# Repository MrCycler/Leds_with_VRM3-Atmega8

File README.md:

# Leds_with_VRM3
Proyecto de manejo de leds con Voice recogniction module V.3 usando un ATMEGA8.

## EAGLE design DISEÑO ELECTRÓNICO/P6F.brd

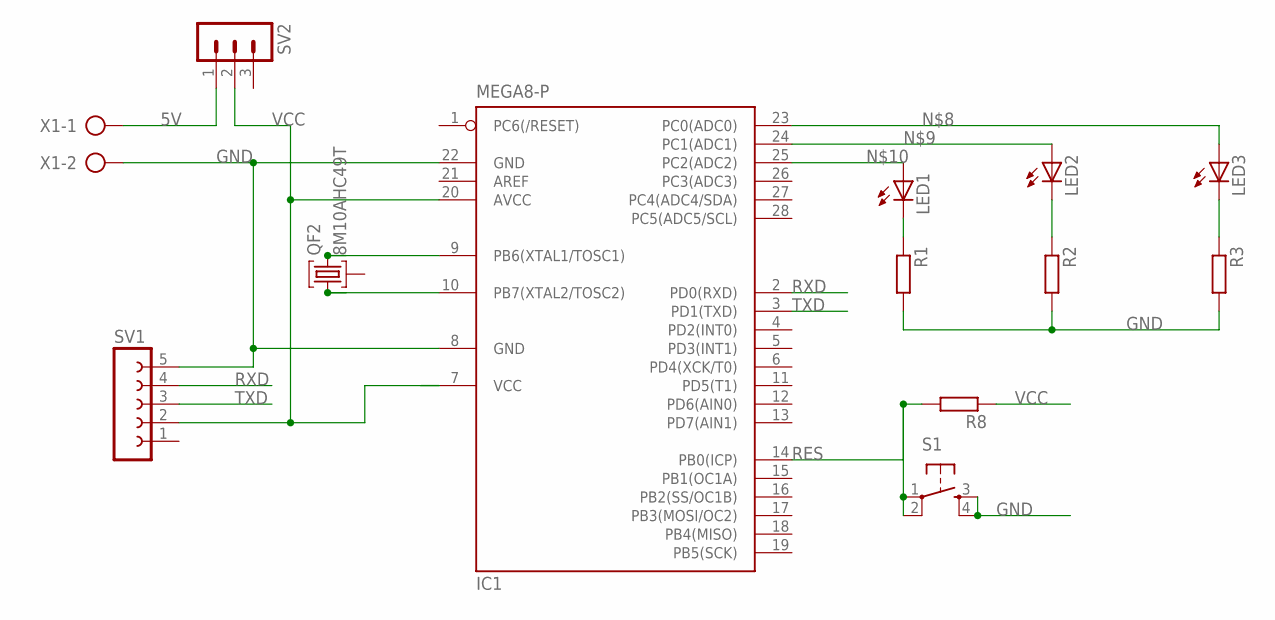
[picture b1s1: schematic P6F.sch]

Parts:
IC1: MEGA8-P; DIL28-3
LED1, LED2, LED3: LED5MM
QF2: 8M10AHC49T; HC49U
R1, R2, R3, R8: R-EU_0204/7; 0204/7
S1: TAC_SWITCHPTH; TACTILE-PTH
SV1: FE05-1
SV2: MA03-1
X1: AK300/2

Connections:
5V: SV2.1, X1.1
GND: IC1.8 (GND), IC1.22 (GND), R1.2, R2.2, R3.2, S1.3, S1.4, SV1.5, X1.2
unnamed: LED1.K (C), R1.1
unnamed: LED2.K (C), R2.1
unnamed: LED3.K (C), R3.1
unnamed: IC1.23 (PC0(ADC0)), LED3.A
unnamed: IC1.24 (PC1(ADC1)), LED2.A
unnamed: IC1.25 (PC2(ADC2)), LED1.A
unnamed: IC1.9 (PB6(XTAL1/TOSC1)), QF2.3
unnamed: IC1.10 (PB7(XTAL2/TOSC2)), QF2.1
RES: IC1.14 (PB0(ICP)), R8.2, S1.1, S1.2
RXD: IC1.2 (PD0(RXD)), SV1.4
TXD: IC1.3 (PD1(TXD)), SV1.3
VCC: IC1.7 (VCC), IC1.20 (AVCC), R8.1, SV1.2, SV2.2

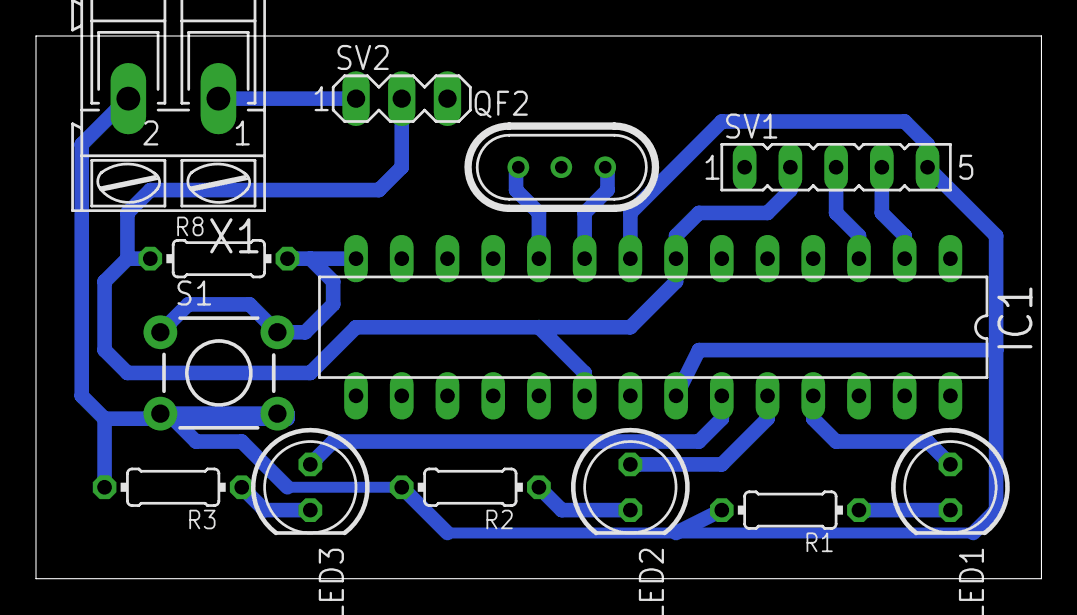
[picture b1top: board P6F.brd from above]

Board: 2 copper layers, 55.9 x 30.1 mm, 13 parts (0 on the bottom side), 14 nets.

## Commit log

2017-11-30 Proyecto Completo

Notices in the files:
parts and their libraries:
SparkFun-Retired: Licensing: Creative Commons ShareAlike 4.0 International - https://creativecommons.org/licenses/by-sa/4.0
